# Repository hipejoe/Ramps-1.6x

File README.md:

Ramps-1.6 or so
===========

forked from ultimachine/Ramps 1.4

terminated AUX doe to space

added libs for tmc2130 watterot with conf0 installed 
add E2
chanded libs f tmc2130 to not use space of unused headers
added supression to endstops but removed 2nd endstop for axis (has tmc2130 so only Z and probe may need one.
re added 2servos
upgraded to 4thermoistors

integrated my previous fan extendr to 5 external outputs
removed VIN (toDO! check arduinos power consumption etc)
changed package or reset + external reset 

changed few Packages to match order
Orderd First Batch PCBs to test

RAMPS 1.6.3 
Got one wirestumb on Zmin fixed
Changed Pins Back to HWSPI 
Added I2C pin Header and HW SPI breakout
added 5vin 

Current status: all up and running thermistors are and endstops are "noisefree" printe is running it for 5month now, got some PCBs left..

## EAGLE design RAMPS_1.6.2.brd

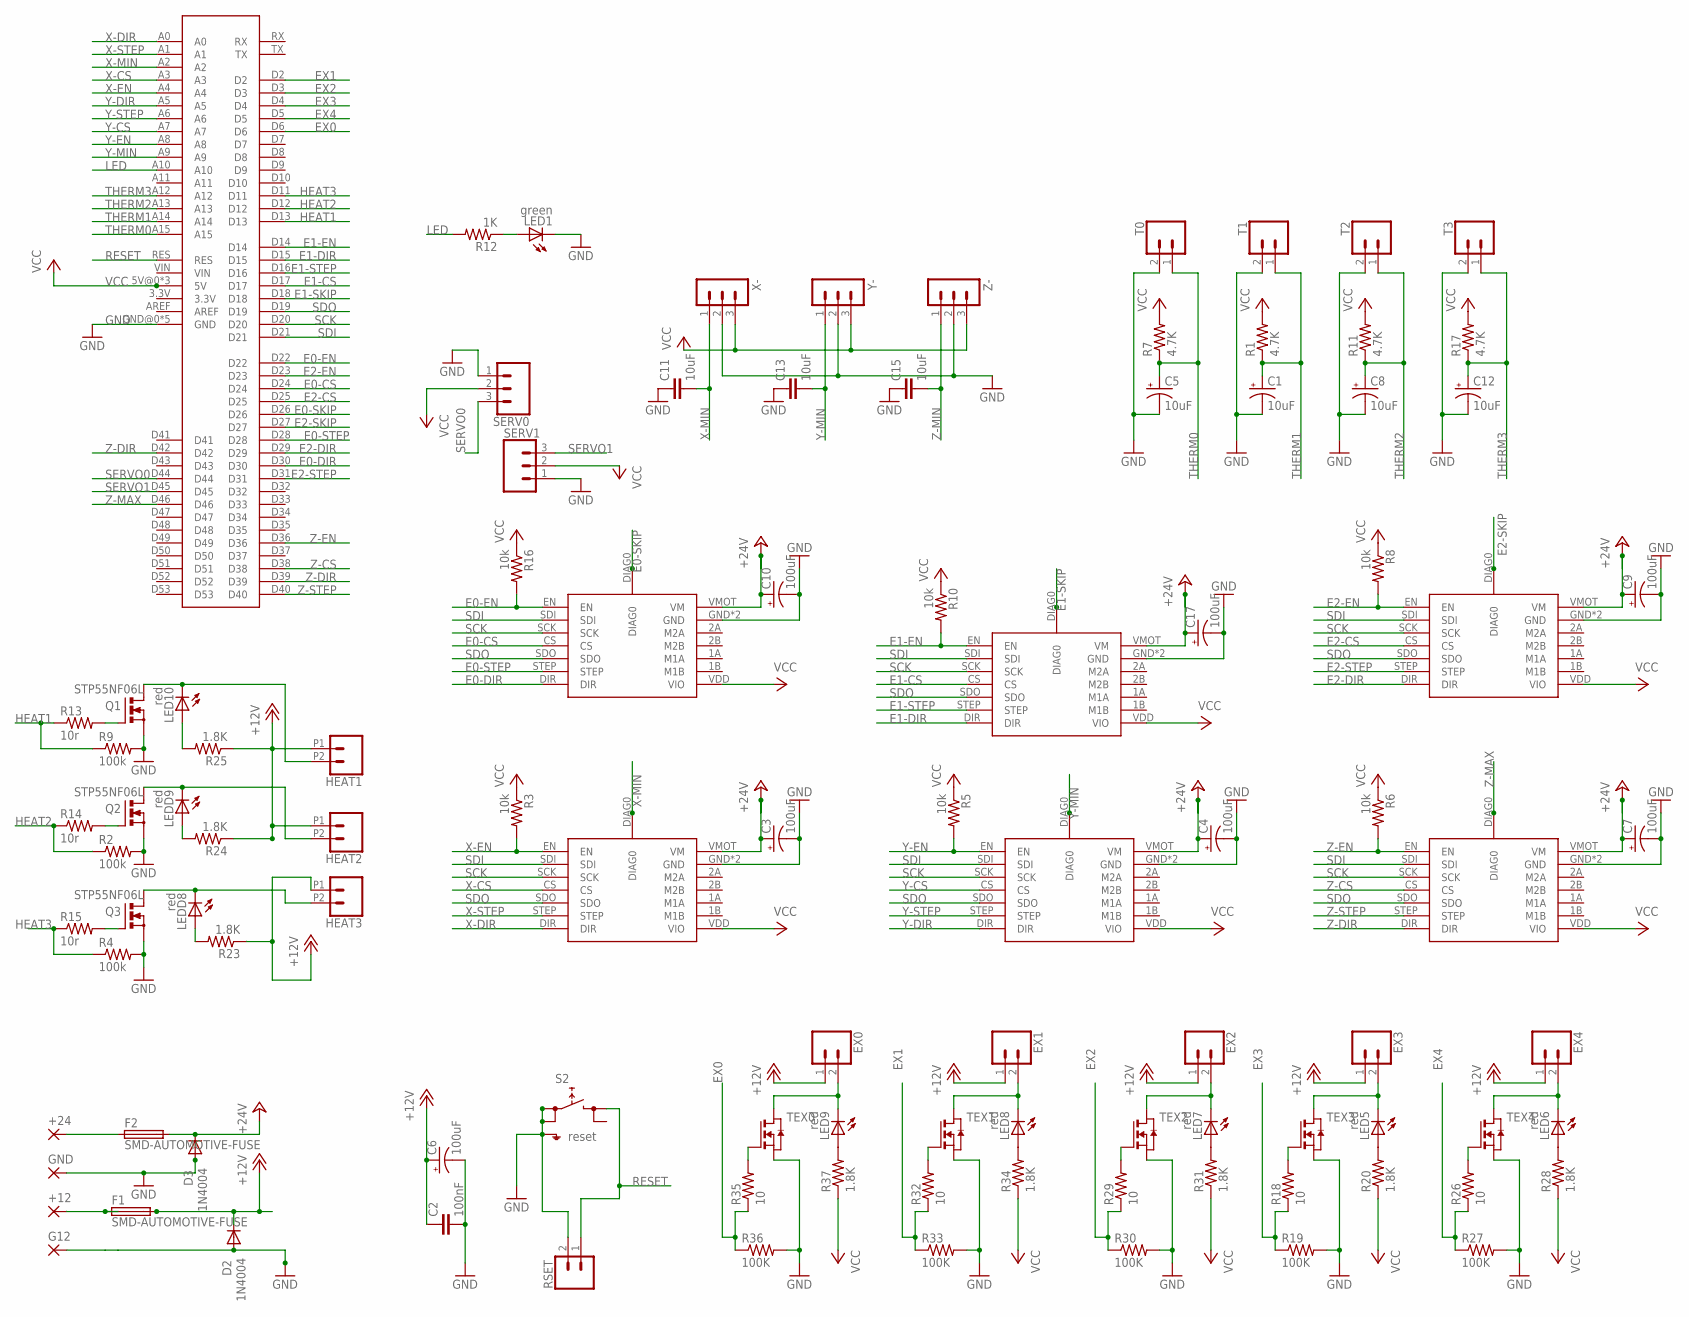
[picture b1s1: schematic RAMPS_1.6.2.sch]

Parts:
+12, +24: 2,15/1,0
C1, C5, C8, C12: 10uF; 153CLV-0405
C2: 100nF; C1206
C3, C4, C6, C7, C9, C10, C17: 100uF; 153CLV-0605
C11, C13, C15: 10uF; C1206
D2, D3: 1N4004; DO41-10
E0, E1, E2: TMC2130DIAG; TMC2130DIAG0
EX0, EX1, EX2, EX3, EX4: CONN_02POLAR_LOCK; MOLEX-1X2_LOCK
F1, F2: SMD-AUTOMOTIVE-FUSE; BLADEFUSE
G12: 2,15/1,0
GND: 2,15/1,0
HEAT1, HEAT2, HEAT3: CONN_022.54MM_SCREWTERM; 1X02_2.54_SCREWTERM
LED1: green; CHIPLED_1206
LED5, LED6, LED7, LED8, LED9, LED10: red; CHIPLED_1206
LEDD8, LEDD9: red; CHIPLED_1206
Q1, Q2, Q3: STP55NF06L; TO220BV
R1, R7, R11, R17: 4.7K; R1206
R2, R4, R9: 100k; R1206
R3, R5, R6, R8, R10, R16: 10k; R1206
R12: 1K; R1206
R13, R14, R15: 10r; R1206
R18, R26, R29, R32, R35: 10; R1206
R19, R27, R30, R33, R36: 100K; R1206
R20, R23, R24, R25, R28, R31, R34, R37: 1.8K; R1206
RSET: CONN_02POLAR_LOCK; MOLEX-1X2_LOCK
S2: reset; SKHMPXE010
SERV0, SERV1: CONN_03; 1X03
T0, T1, T2, T3: CONN_02LOCK; 1X02_LOCK
TEX0, TEX1, TEX2, TEX3, TEX4: NMOSSOT223; SOT223
U$1: ARDUINOSHIELD; REPRAPJR_ARDUINO_MEGA_SHIELD
X: TMC2130DIAG; TMC2130DIAG0
X-: 3PIN-HEADER
Y: TMC2130DIAG; TMC2130DIAG0
Y-: 3PIN-HEADER
Z: TMC2130DIAG; TMC2130DIAG0
Z-: 3PIN-HEADER

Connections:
+12V: C2.1, C6.+, D2.C, EX0.1, EX1.1, EX2.1, EX3.1, EX4.1, F1.2, F1.P$5, F1.P$6, F1.P$7, F1.P$8, HEAT1.P1 (1), HEAT2.P1 (1), HEAT3.P1 (1), R23.1, R24.1, R25.1
+24V: C3.+, C4.+, C7.+, C9.+, C10.+, C17.+, D3.C, E0.VMOT (VM), E1.VMOT (VM), E2.VMOT (VM), F2.2, F2.P$5, F2.P$6, F2.P$7, F2.P$8, X.VMOT (VM), Y.VMOT (VM), Z.VMOT (VM)
E0-CS: E0.CS, U$1.D24
E0-DIR: E0.DIR, U$1.D30
E0-EN: E0.EN, R16.2, U$1.D22
E0-SKIP: E0.DIAG0, U$1.D26
E0-STEP: E0.STEP, U$1.D28
E1-CS: E1.CS, U$1.D17
E1-DIR: E1.DIR, U$1.D15
E1-EN: E1.EN, R10.2, U$1.D14
E1-SKIP: E1.DIAG0, U$1.D18
E1-STEP: E1.STEP, U$1.D16
E2-CS: E2.CS, U$1.D25
E2-DIR: E2.DIR, U$1.D29
E2-EN: E2.EN, R8.2, U$1.D23
E2-SKIP: E2.DIAG0, U$1.D27
E2-STEP: E2.STEP, U$1.D31
EX0: R35.1, R36.1, U$1.D6
EX1: R32.1, R33.1, U$1.D2
EX2: R29.1, R30.1, U$1.D3
EX3: R18.1, R19.1, U$1.D4
EX4: R26.1, R27.1, U$1.D5
GND: C1.-, C2.2, C3.-, C4.-, C5.-, C6.-, C7.-, C8.-, C9.-, C10.-, C11.1, C12.-, C13.1, C15.1, C17.-, D2.A, D3.A, E0.GND, E0.GND@0 (GND), E1.GND, E1.GND@0 (GND), E2.GND, E2.GND@0 (GND), G12.1, GND.1, LED1.C, Q1.S, Q2.S, Q3.S, R2.2, R4.2, R9.2, R19.2, R27.2, R30.2, R33.2, R36.2, RSET.2, S2.1 (1.1), S2.2 (1.2), SERV0.1, SERV1.1, T0.2, T1.2, T2.2, T3.2, TEX0.3 (S), TEX1.3 (S), TEX2.3 (S), TEX3.3 (S), TEX4.3 (S), U$1.GND@0 (GND), U$1.GND@1 (GND), U$1.GND@2 (GND), U$1.GND@3 (GND), U$1.GND@4 (GND), X.GND, X.GND@0 (GND), X-.2, Y.GND, Y.GND@0 (GND), Y-.2, Z.GND, Z.GND@0 (GND), Z-.2; also elsewhere on the board
HEAT1: R9.1, R13.1, U$1.D13
HEAT2: R2.1, R14.1, U$1.D12
HEAT3: R4.1, R15.1, U$1.D11
LED: R12.2, U$1.A10
unnamed: HEAT2.P2 (2), LEDD9.C, Q2.D
unnamed: R18.2, TEX3.1 (G)
unnamed: HEAT1.P2 (2), LED10.C, Q1.D
unnamed: EX3.2, LED5.C, TEX3.2 (D), TEX3.4 (D)
unnamed: LED5.A, R20.2
unnamed: EX2.2, LED7.C, TEX2.2 (D), TEX2.4 (D)
unnamed: R26.2, TEX4.1 (G)
unnamed: EX4.2, LED6.C, TEX4.2 (D), TEX4.4 (D)
unnamed: LEDD8.A, R23.2
unnamed: LED6.A, R28.2
unnamed: R29.2, TEX2.1 (G)
unnamed: LED7.A, R31.2
unnamed: R32.2, TEX1.1 (G)
unnamed: EX1.2, LED8.C, TEX1.2 (D), TEX1.4 (D)
unnamed: LED8.A, R34.2
unnamed: R35.2, TEX0.1 (G)
unnamed: LEDD9.A, R24.2
unnamed: LED1.A, R12.1
unnamed: Q2.G, R14.2
unnamed: Q1.G, R13.2
unnamed: Q3.G, R15.2
unnamed: LED10.A, R25.2
unnamed: HEAT3.P2 (2), LEDD8.C, Q3.D
unnamed: +24.1, F2.1, F2.P$1, F2.P$2, F2.P$3, F2.P$4
unnamed: +12.1, F1.1, F1.P$1, F1.P$2, F1.P$3, F1.P$4
unnamed: EX0.2, LED9.C, TEX0.2 (D), TEX0.4 (D)
unnamed: LED9.A, R37.2
RESET: RSET.1, S2.3 (2.1), U$1.RES; also elsewhere on the board
SCK: E0.SCK, E1.SCK, E2.SCK, U$1.D20, X.SCK, Y.SCK, Z.SCK
SDI: E0.SDI, E1.SDI, E2.SDI, U$1.D21, X.SDI, Y.SDI, Z.SDI
SDO: E0.SDO, E1.SDO, E2.SDO, U$1.D19, X.SDO, Y.SDO, Z.SDO
SERVO0: SERV0.3, U$1.D44
SERVO1: SERV1.3, U$1.D45
THERM0: C5.+, R7.1, T0.1, U$1.A15
THERM1: C1.+, R1.1, T1.1, U$1.A14
THERM2: C8.+, R11.1, T2.1, U$1.A13
THERM3: C12.+, R17.1, T3.1, U$1.A12
VCC: E0.VDD (VIO), E1.VDD (VIO), E2.VDD (VIO), R1.2, R3.1, R5.1, R6.1, R7.2, R8.1, R10.1, R11.2, R16.1, R17.2, R20.1, R28.1, R31.1, R34.1, R37.1, SERV0.2, SERV1.2, U$1.5V@0 (5V), U$1.5V@1 (5V), U$1.5V@2 (5V), X.VDD (VIO), X-.3, Y.VDD (VIO), Y-.3, Z.VDD (VIO), Z-.3
X-CS: U$1.A3, X.CS
X-DIR: U$1.A0, X.DIR
X-EN: R3.2, U$1.A4, X.EN
X-MIN: C11.2, U$1.A2, X.DIAG0, X-.1
X-STEP: U$1.A1, X.STEP
Y-CS: U$1.A7, Y.CS
Y-DIR: U$1.A5, Y.DIR
Y-EN: R5.2, U$1.A8, Y.EN
Y-MIN: C13.2, U$1.A9, Y.DIAG0, Y-.1
Y-STEP: U$1.A6, Y.STEP
Z-CS: U$1.D38, Z.CS
Z-DIR: U$1.D39, U$1.D42, Z.DIR
Z-EN: R6.2, U$1.D36, Z.EN
Z-MAX: U$1.D46, Z.DIAG0
Z-MIN: C15.2, Z-.1
Z-STEP: U$1.D40, Z.STEP

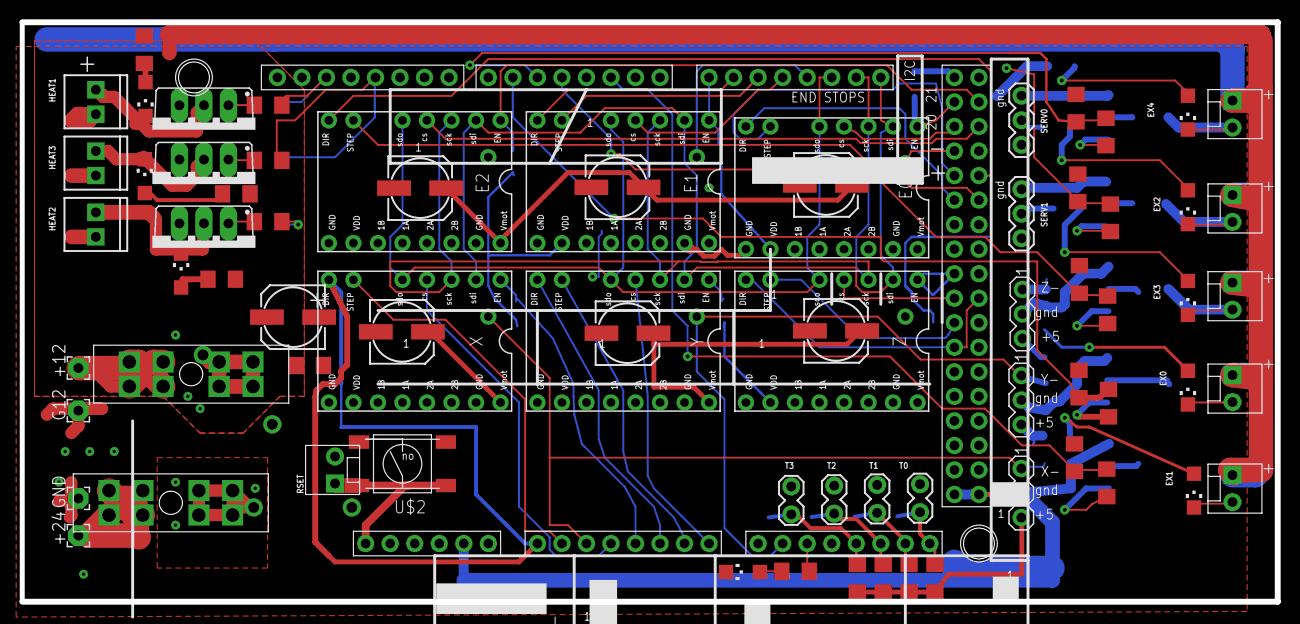
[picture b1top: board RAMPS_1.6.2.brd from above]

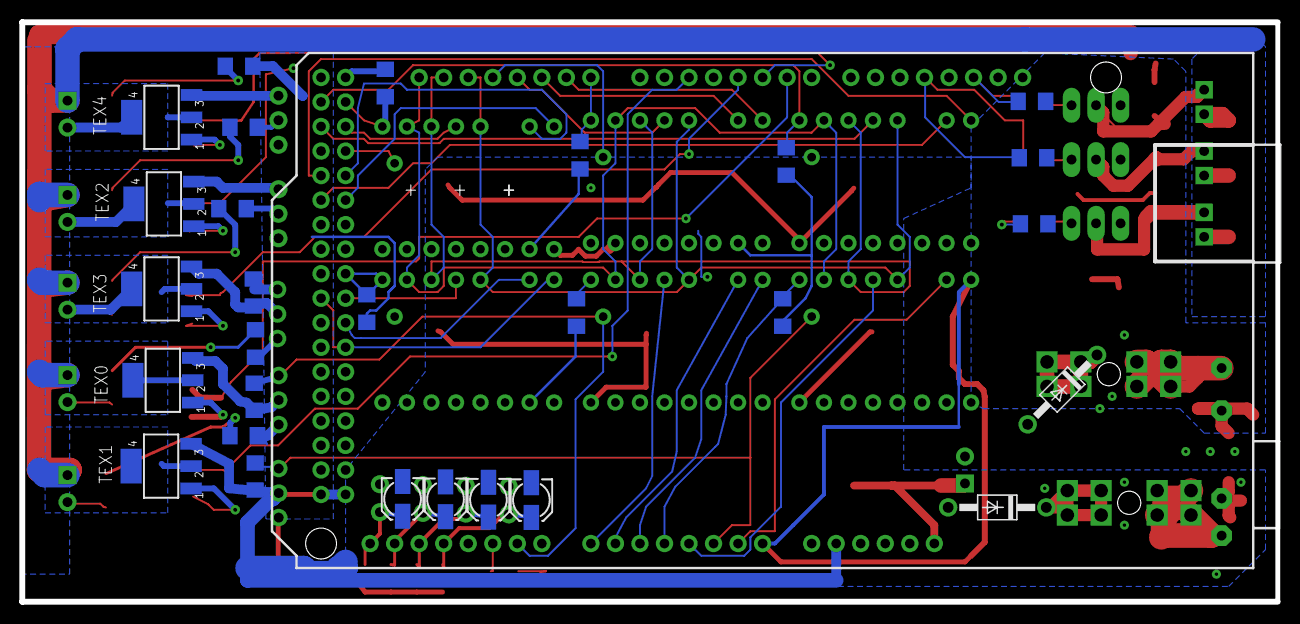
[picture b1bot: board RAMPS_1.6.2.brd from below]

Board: 4 copper layers, 130.0 x 60.0 mm, 101 parts (28 on the bottom side), 81 nets.

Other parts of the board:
U$2: RS-TASTER; RS-SWITCH

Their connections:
GND: U$2.P$1, U$2.P$2; also elsewhere on the board
RESET: U$2.P$3, U$2.P$4; also elsewhere on the board

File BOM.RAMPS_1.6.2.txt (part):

Stückliste exportiert aus D:/Documents/PCB/eagle/eagle/proj/RAMTPB/Ramps-1.4.2-master/RAMPS_1.6.2.sch am 22.07.2018 23:47

Qty Value               Device                  Package                      Parts                         Description                                                                                                     MF MPN OC_FARNELL OC_NEWARK SF_ID     SPICEPREFIX
4                       2,15/1,0                2,15/1,0                     +12, +24, G12, GND            THROUGH-HOLE PAD                                                                                                                                                 
3                       3PIN-HEADER             3PIN-HEADER                  X-, Y-, Z-                    PIN HEADER                                                                                                                                                       
3                       CONN_022.54MM_SCREWTERM 1X02_2.54_SCREWTERM          HEAT1, HEAT2, HEAT3           Multi connection point. Often used as Generic Header-pin footprint for 0.1 inch spaced/style header connections                                                  
4                       CONN_02LOCK             1X02_LOCK                    T0, T1, T2, T3                Multi connection point. Often used as Generic Header-pin footprint for 0.1 inch spaced/style header connections                                                  
6                       CONN_02POLAR_LOCK       MOLEX-1X2_LOCK               EX0, EX1, EX2, EX3, EX4, RSET Multi connection point. Often used as Generic Header-pin footprint for 0.1 inch spaced/style header connections                             PRT-09918 B          
2                       CONN_03                 1X03                         SERV0, SERV1                  Multi connection point. Often used as Generic Header-pin footprint for 0.1 inch spaced/style header connections                                                  
5                       NMOSSOT223              SOT223                       TEX0, TEX1, TEX2, TEX3, TEX4  MOS FET                                                                                                                unknown    unknown             J          
3   1.8K                R-US_R1206              R1206                        R23, R24, R25                 RESISTOR, American symbol                                                                                                                                        
5   1.8K                R-US_R1206              R1206                        R20, R28, R31, R34, R37       RESISTOR, American symbol                                                                                                                             R          
5   10                  R-US_R1206              R1206                        R18, R26, R29, R32, R35       RESISTOR, American symbol                                                                                                                             R          
1   100K                R-US_R1206              R1206                        R19                           RESISTOR, American symbol                                                                                                                             L          
4   100K                R-US_R1206              R1206                        R27, R30, R33, R36            RESISTOR, American symbol                                                                                                                             R          
3   100k                R-US_R1206              R1206                        R2, R4, R9                    RESISTOR, American symbol                                                                                                                                        
1   100nF               C-EUC1206               C1206                        C2                            CAPACITOR, European symbol                                                                                                                                       
7   100uF               CPOL-US153CLV-0605      153CLV-0605                  C3, C4, C6, C7, C9, C10, C17  POLARIZED CAPACITOR, American symbol                                                                                                                             
6   10k                 R-US_R1206              R1206                        R3, R5, R6, R8, R10, R16      RESISTOR, American symbol                                                                                                                                        
3   10r                 R-US_R1206              R1206                        R13, R14, R15                 RESISTOR, American symbol                                                                                                                                        
3   10uF                C-EUC1206               C1206                        C11, C13, C15                 CAPACITOR, European symbol                                                                                                                                       
4   10uF                CPOL-US153CLV-0405      153CLV-0405                  C1, C5, C8, C12               POLARIZED CAPACITOR, American symbol                                                                                                                             
1   1K                  R-US_R1206              R1206                        R12                           RESISTOR, American symbol                                                                                                                                        
2   1N4004              1N4004                  DO41-10                      D2, D3                        DIODE                                                                                                                                                            
4   4.7K                R-US_R1206              R1206                        R1, R7, R11, R17              RESISTOR, American symbol                                                                                                                                        
1   ARDUINOSHIELD       ARDUINOSHIELD           REPRAPJR_ARDUINO_MEGA_SHIELD U$1                           aus schaltplan kopierte version von amega                                                                                                                        
2   SMD-AUTOMOTIVE-FUSE SMD-AUTOMOTIVE-FUSE     BLADEFUSE                    F1, F2                        Surface mount fuse holder for kfz blade fuses                                                                                                                    
3   STP55NF06L          IRF512                  TO220BV                      Q1, Q2, Q3                    N-CHANNEL MOS FET                                                                                                                                                
6   TMC2130DIAG         TMC2130DIAG             TMC2130DIAG0                 E0, E1, E2, X, Y, Z                                                                                                                                                                            
1   green               LEDCHIPLED_1206         CHIPLED_1206                 LED1                          LED                                                                                                                                                              
3   red                 LEDCHIPLED_1206         CHIPLED_1206                 LED10, LEDD8, LEDD9           LED                                                                                                                                                              
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
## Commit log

2018-07-18 add new files from last few months
2018-07-18 added images of current copper.
2018-07-22 BOM added
2018-07-22 changed package to 1206 on R and C
2018-07-27 added BOM included Prices
    can all be ordered via Reichelt
2018-07-27 changed few componments for Order
2018-08-02 Gerbers for first produktion

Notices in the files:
RAMPS_1.6.2.brd:
GPL v3
Copyright 2011 Johnny Russell - UltiMachine
parts and their libraries:
SparkFun-Connectors: Licensing: Creative Commons ShareAlike 4.0 International - https://creativecommons.org/licenses/by-sa/4.0
